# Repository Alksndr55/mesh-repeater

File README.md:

<div align="center">

# Mesh Repeater

### Плата LoRa-репитера для MeshCore и Meshtastic

**v1.26 · одна плата · 90 × 100 мм**

Солнечное питание · Na-ion 1S / LTO 2S · аппаратный watchdog

[Скачать готовый комплект](https://github.com/Alksndr55/mesh-repeater/releases/download/v1.26/Mesh_Repeater_v1.26_KiCad.zip) · [Релиз v1.26](https://github.com/Alksndr55/mesh-repeater/releases/tag/v1.26) · [Двухплатная версия v2](https://github.com/Alksndr55/mesh-repeater-2.0)

*3D-рендер проекта KiCad v1.26. Состав устанавливаемых компонентов зависит от выбранного варианта сборки.*

</div>

Mesh Repeater объединяет радиочасть, солнечный зарядник, питание и служебные узлы на одной плате. Устройство предназначено для самостоятельной сборки и питания от аккумулятора и солнечной панели.

**Главные цели проекта — максимальное энергосбережение и работа в суровых сибирских зимах.**

Ведущее исполнение **v1** удобно для монтажа и обслуживания: все узлы доступны на одной плате, без межплатного соединителя. Исходники KiCad, перечень компонентов и материалы для сборки входят в готовый комплект.

## Что предусмотрено

| Узел | Назначение |
|---|---|
| **nRF52840 + LoRa** | Доработанный NiceNano, модуль HT-RA62 на SX1262, антенный разъём SMA и место под фильтр FL1. |
| **Солнечный зарядник** | CN3722 с настройкой рабочей точки солнечной панели. |
| **Na-ion 1S или LTO 2S** | Три варианта комплектации: Na-ion 1S с COLD, Na-ion 1S без COLD, LTO 2S с пассивной балансировкой. |
| **Питание 3,3 В** | Повышающе-понижающий TPS63802, двухступенчатый LC-фильтр и отдельная ветвь питания радиомодуля. |
| **Контроль аккумулятора** | INA219 измеряет напряжение и ток в основном тракте аккумулятора. |
| **Часы и watchdog** | DS3231M с резервом от CR2032; ATtiny13A следит за активностью TXEN и может сбросить основной процессор. |
| **Подключение и обслуживание** | Разъём внешнего GPS, I²C и UART с логикой 3,3 В, AVR ISP, кнопки USER/RESET и контрольные точки. |

### Опциональный фильтр антенны

На MAIN предусмотрено место **FL1** для полосового SAW-фильтра **S869M000S003**. Он ослабляет внеполосные сигналы. В полосе 868–870 МГц паспортные потери составляют до 2,5 дБ. Штатный тракт проходит через медную перемычку **NT1**. Перед монтажом FL1 перемычку разрезают по инструкции и ограничивают мощность на входе фильтра до **+13 дБм**.

Рабочая температура этого фильтра **−10…+65 °C**. Для более холодных установок сохраняют штатный обход NT1. [Паспорт фильтра](https://abracon.com/datasheets/AEL-Crystals/PN/S869M000S003.pdf) · [Монтаж FL1](docs/ASSEMBLY_COMMON_RU.md)

## Совместимость с MeshCore и Meshtastic

Радиомодуль HT-RA62 (SX1262 с TCXO) подключён по распиновке **FakeTec / ProMicro nRF52840**. Для обеих версий платы подходят следующие профили прошивок.

| Прошивка | Профиль | Конфигурация |
|---|---|---|
| **MeshCore** | ProMicro nRF52840, сборка `ProMicro_repeater` | [MeshCore ProMicro](https://github.com/meshcore-dev/MeshCore/blob/repeater-v1.18.0/variants/promicro/platformio.ini#L40-L53) |
| **Meshtastic** | NRF52 Pro-micro DIY с TCXO, сборка `nrf52_promicro_diy_tcxo` | [Meshtastic ProMicro TCXO](https://github.com/meshtastic/firmware/blob/v2.7.26.54e0d8d/variants/nrf52840/diy/nrf52_promicro_diy_tcxo/platformio.ini) |

Совместимость проверена по распиновке и конфигурациям сборок. Показания напряжения аккумулятора калибруют под делитель платы **1:2**. Для Na-ion 1S и LTO 2S шкалу процента заряда адаптируют под химию и число ячеек. При подключении внешнего UART к J5 сверяют назначение RX и TX с выбранной прошивкой.

## Варианты сборки

| Вариант | Комплектация |
|---|---|
| **Na-ion 1S · COLD** | Узел температурного ограничения зарядного тока установлен. |
| **Na-ion 1S · без COLD** | Сборка без узла COLD. |
| **LTO · 2S** | Две последовательные ячейки LTO и пассивные балансиры. |

Вариант задаётся номиналами и составом деталей по BOM. Это выбор при сборке, а не переключение химии аккумулятора одной перемычкой. Условия заряда выбирают по паспорту конкретных ячеек; схема LTO не заменяет полноценную BMS.

### COLD — ограничение тока заряда на холоде

В сборке Na-ion 1S с COLD датчик TH1 задаёт температурный режим солнечного зарядника CN3722. При охлаждении схема включает дополнительный шунт R56 в цепь измерения тока. Расчётный предел зарядного тока снижается примерно с **0,67 А до 0,10 А**. При потеплении возвращается обычный режим.

Расчётный порог снижения тока — **−17,4 °C**, возврата — **−14,5 °C**. Разница между порогами помогает избежать частых переключений при колебаниях температуры. Один датчик TH1 устанавливают на плате или выносят к аккумулятору. Допустимый ток и температуру заряда сверяют с паспортом конкретной ячейки. [Общая инструкция по сборке](docs/ASSEMBLY_COMMON_RU.md)

### Watchdog — автоматический перезапуск репитера

Отдельный ATtiny13A с прошивкой watchdog v1.00 следит за сигналом **TXEN**, который показывает включение передатчика LoRa. Каждое новое включение передатчика запускает отсчёт заново. Между событиями контроллер спит в режиме Power-down. Когда время ожидания истекает, ATtiny13A подаёт импульс RESET на nRF52840. После сброса выбранная прошивка загружается заново и инициализирует радиомодуль.

При 3,3 В и комнатной температуре расчётные ориентиры составляют около **3,5 часа** ожидания и **1,2 секунды** сброса. При длительном молчании радиомодуля или застрявшем высоком TXEN тайм-аут тоже срабатывает. [Подключение и прошивка watchdog](v1/design/watchdog_reference/INTEGRATION_RU.txt)

## От схемы — к детали на плате

В ZIP уже включён **portable NexusBV**. Запуск `START.cmd` открывает меню с CAD и PDF-схемой нужной сборки. Двойной щелчок по обозначению или свободной части тела символа в PDF помогает найти компонент на бордвью.

- Два CAD: **NaIon_COLD** и **LTO_2S**, с номиналами и отметками DNP.
- PDF-схемы, BOM и инструкции по сборке.
- Проект KiCad 10 с локальными посадочными местами и всеми используемыми 3D-моделями.
- Watchdog v1.00: исходники, HEX и инструкция прошивки.

<details>
<summary><strong>Посмотреть обратную сторону платы</strong></summary>

</details>

## С чего начать

1. Скачайте **Mesh_Repeater_v1.26_KiCad.zip** из [релиза](https://github.com/Alksndr55/mesh-repeater/releases/tag/v1.26) и полностью распакуйте его.
2. Для просмотра запустите `START.cmd` в Windows; для редактирования откройте [проект MAIN](v1/design/Meshcore_NaIon/Meshcore_NaIon.kicad_pro) в KiCad 10.
3. Выберите вариант аккумулятора и собирайте плату по [BOM](v1/bom/COMPONENT_BOM.csv) и [общей инструкции](docs/ASSEMBLY_COMMON_RU.md).

**Перед первым включением:** модуль NiceNano требует указанной в инструкции доработки питания. Перед подключением USB нужно снять шунт **J11**, а вернуть его после отключения USB. J8 и J12 соединены с общей BAT: независимые аккумуляторы к ним одновременно не подключают.

## Документация

[Общая схема PDF](shared/output/pdf/MeshRepeater_schematic.pdf) · [Схема KiCad](shared/schematic/MeshRepeater.kicad_pro) · [Сборка v1](v1/docs/ASSEMBLY_RU.md) · [Аппаратные ограничения](docs/LIMITATIONS_RU.md) · [Изменения выпуска](https://github.com/Alksndr55/mesh-repeater/releases/tag/v1.26)

<details>
<summary><strong>Статус проекта и проверки</strong></summary>

Это предварительный инженерный выпуск. Для точных файлов v1.26 проверены общая схема, BOM, ERC/DRC, соответствие платы схеме и комплектность архива. Эти проверки не заменяют испытания собранного устройства: дальность связи, автономность, температурные режимы и работа конкретных модулей здесь не заявляются как измеренные характеристики.

[Отчёт проверок](v1/audit/current/checks.json) · [Экспорт CAD/PDF](v1/audit/current/exports.json) · [Манифест файлов](RELEASE_MANIFEST.json)

</details>

---

**Designed by @Alksndritm** · [Alksndr55](https://github.com/Alksndr55)

Собственные материалы — [CC BY-NC-SA 4.0](v1/LICENSE.md). Сторонние компоненты, модели и программы сохраняют свои лицензии.

Проекты прошивок — [MeshCore](https://github.com/meshcore-dev/MeshCore) и [Meshtastic](https://github.com/meshtastic/firmware).

## Поддержать проект

**Осциллограф Siglent SDS1204X HD.** Пульсации любят прятаться между цифрами мультиметра. Осциллограф поможет их поймать и проверить питание при запуске и передаче.

[Скинуться на осциллограф через Т‑Банк](https://t.tb.ru/pm_short/89zrJmEhG7B)

**Микроскоп Leica IVESTA 3.** У припоя иногда свой план монтажа. Под микроскопом удобнее паять мелкие детали и вовремя замечать перемычки между выводами.

[Скинуться на микроскоп через Сбер](https://messenger.sbrf.ru/sl/KsiFZJu4xBxTLGTPz)

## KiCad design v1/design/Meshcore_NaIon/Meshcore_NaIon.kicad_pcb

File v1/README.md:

# Mesh Repeater v1.26

Designed by @Alksndritm. Текущее исполнение общего проекта.
Ведущая разводка.
Предыдущий опубликованный выпуск от 30.10.2026: [v1.25 на GitHub](https://github.com/Alksndr55/mesh-repeater/releases/tag/v1.25).
Предыдущая публикация — [v1.22](https://github.com/Alksndr55/mesh-repeater/releases/tag/v1.22)
(прежнее обозначение S4.22). Локальная редакция от 06.11.2026 — v1.26. Следующий номер — v1.27.

[MAIN](design/Meshcore_NaIon/Meshcore_NaIon.kicad_pro)

[Общая схема](../shared/schematic/MeshRepeater.kicad_pro) ·
[BOM](bom/COMPONENT_BOM.csv) · [Сборка](docs/ASSEMBLY_RU.md) ·
[Порядок выпуска](../docs/WORKFLOW_RU.md) · [Лицензия](LICENSE.md).

Текущие экспорты находятся в output/current, проверки — в audit/current.
Версия и состав задаются корневым project.json. CAD остаётся редактируемым;
общий процесс выпуска сохраняет геометрию и проверяет соответствие общей схеме.
Опубликованные исторические теги сохраняют свои прежние имена.

Дорожки и GND-переходы приведены к [общим правилам](../docs/ROUTING_RULES_RU.md).
[Результат и исключения сетки](../docs/ROUTING_RESULT_RU.md).
Включён [watchdog v1.00](design/watchdog_reference/INTEGRATION_RU.txt)
с каноническими исходником и HEX; LFUSE=0x73, HFUSE=0xFB, ISP 100 мкс.
Локальный архив этого выпуска создаётся в `../releases/v1.26/`.

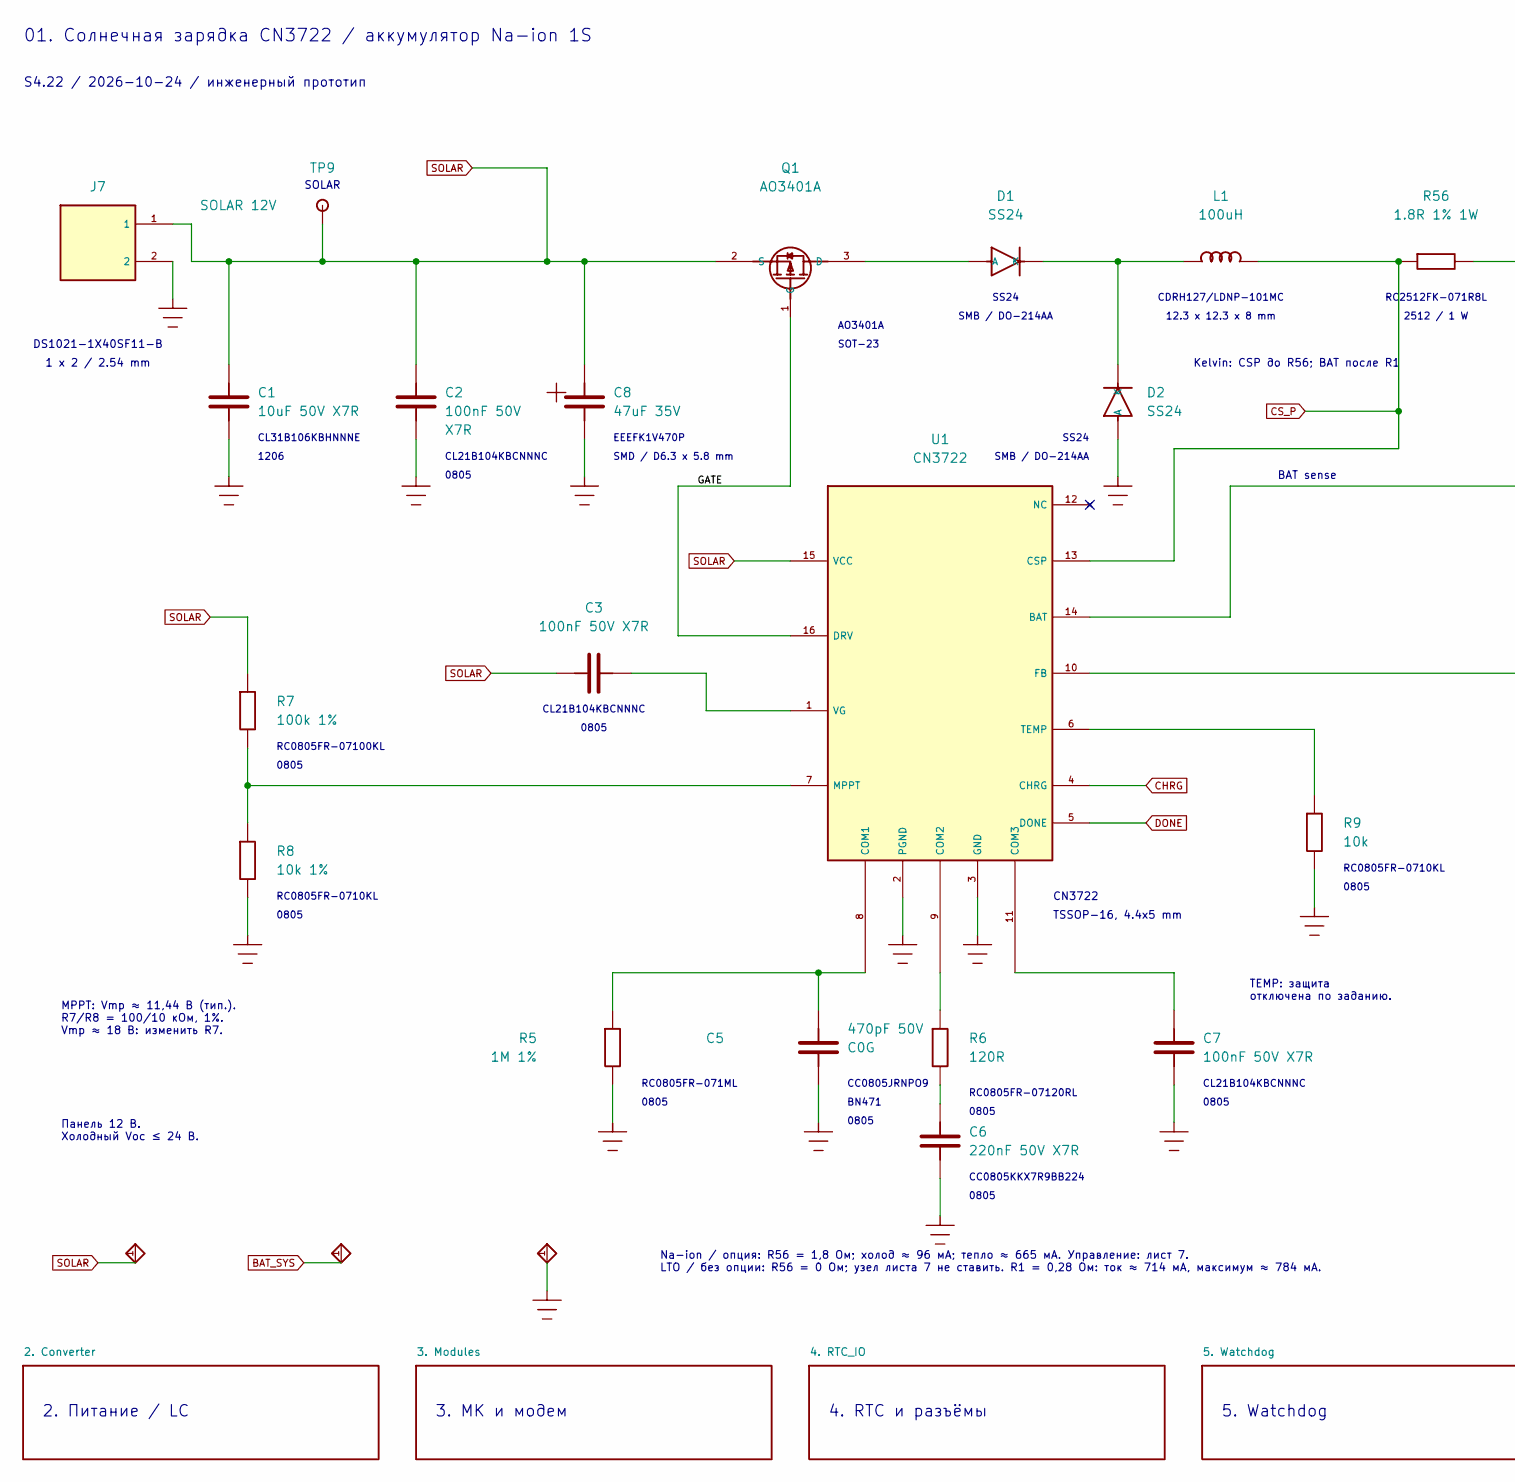
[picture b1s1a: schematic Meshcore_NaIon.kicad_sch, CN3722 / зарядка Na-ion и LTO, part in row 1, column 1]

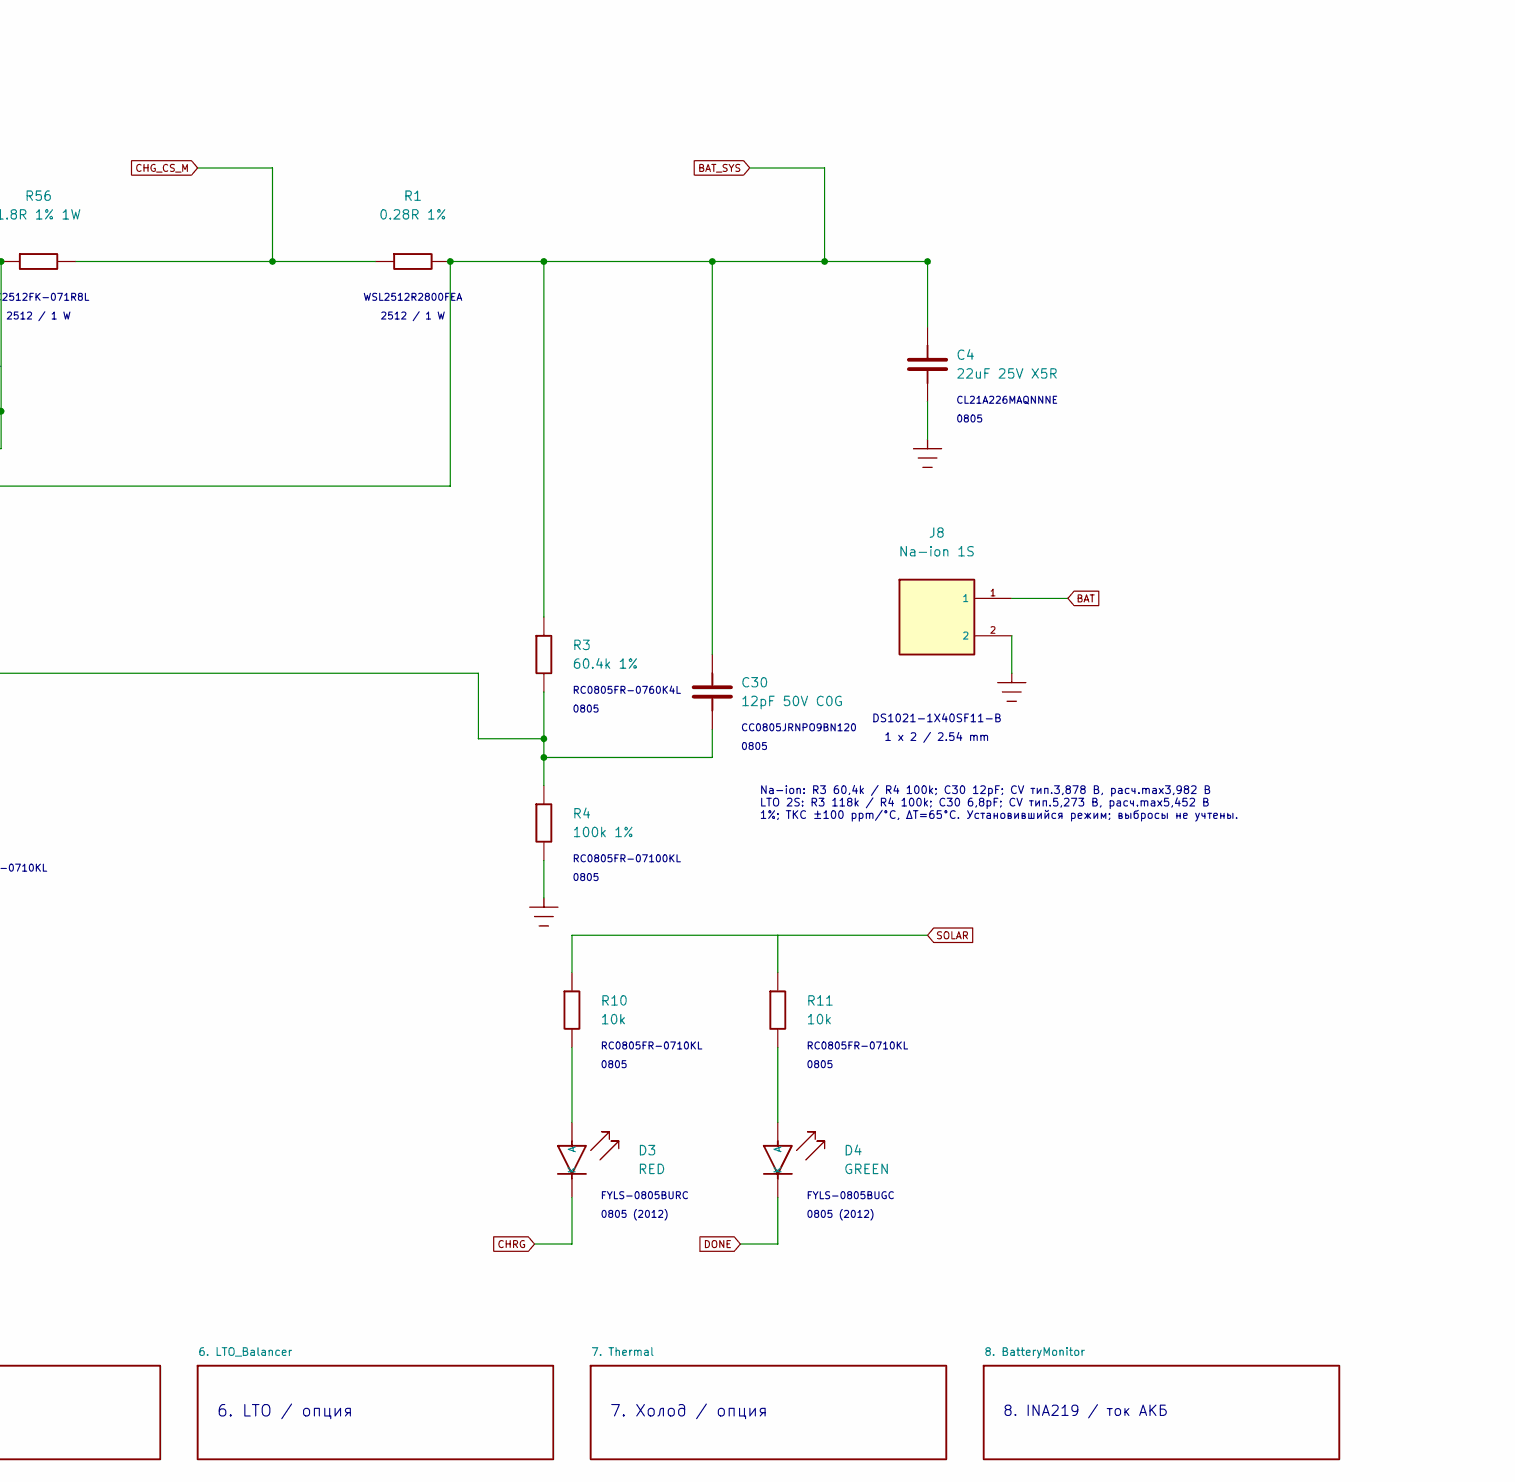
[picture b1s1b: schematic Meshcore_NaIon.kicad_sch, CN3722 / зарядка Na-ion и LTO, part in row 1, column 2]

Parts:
C1: 10uF 50V X7R; C_1206_3216Metric; MPN CL31B106KBHNNNE
C2, C3, C7: 100nF 50V X7R; C_0805_2012Metric; MPN CL21B104KBCNNNC
C4: 22uF 25V X5R; C_0805_2012Metric; MPN CL21A226MAQNNNE
C5: 470pF 50V C0G; C_0805_2012Metric; MPN CC0805JRNPO9BN471
C6: 220nF 50V X7R; C_0805_2012Metric; MPN CC0805KKX7R9BB224
C8: 47uF 35V; CP_Elec_Panasonic_FK_D_6.3x5.8; MPN EEEFK1V470P
C30: 12pF 50V C0G; C_0805_2012Metric; MPN CC0805JRNPO9BN120
D1, D2: SS24; D_SMB; MPN SS24
D3: RED; LED_0805_2012Metric; MPN FYLS-0805BURC
D4: GREEN; LED_0805_2012Metric; MPN FYLS-0805BUGC
J7: SOLAR 12V; PinHeader_1x02_P2.54mm_Vertical; MPN DS1021-1X40SF11-B
J8: Na-ion 1S; PinHeader_1x02_P2.54mm_Vertical; MPN DS1021-1X40SF11-B
L1: 100uH; L_Sumida_CDRH127_LDNP_101MC; MPN CDRH127/LDNP-101MC
Q1: AO3401A; SOT-23; MPN AO3401A
R1: 0.28R 1%; R_Vishay_WSL2512_A3__A3_R1; MPN WSL2512R2800FEA
R3: 60.4k 1%; R_0805_2012Metric; MPN RC0805FR-0760K4L; LCSC C2084414
R4: 100k 1%; R_0805_2012Metric; MPN RC0805FR-07100KL; LCSC C110775
R5: 1M 1%; R_0805_2012Metric; MPN RC0805FR-071ML
R6: 120R; R_0805_2012Metric; MPN RC0805FR-07120RL
R7: 100k 1%; R_0805_2012Metric; MPN RC0805FR-07100KL; LCSC C856623
R8: 10k 1%; R_0805_2012Metric; MPN RC0805FR-0710KL
R9, R10, R11: 10k; R_0805_2012Metric; MPN RC0805FR-0710KL
R56: 1.8R 1% 1W; R_2512_6332Metric__A3_R56; MPN RC2512FK-071R8L
TP9: SOLAR; TestPoint_Pad_D1.5mm; MPN PCB test pad / not purchased
U1: CN3722; TSSOP-16_4.4x5mm_P0.65mm; MPN CN3722; LCSC C77905

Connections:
/GATE: Q1.1 (G), U1.16 (DRV)
BAT: J8.1; also elsewhere on the board
BAT_SYS: C4.1, C30.1, R1.2, R3.1, U1.14 (BAT); also elsewhere on the board
CHG_CS_M: R1.1, R56.2; also elsewhere on the board
CHRG: D3.1 (K), U1.4 (CHRG)
CS_P: L1.2, R56.1, U1.13 (CSP); also elsewhere on the board
DONE: D4.1 (K), U1.5 (DONE)
GND: C1.2, C2.2, C4.2, C5.2, C6.2, C7.2, C8.2, D2.2 (A), J7.2, J8.2, R4.2, R5.2, R8.2, R9.2, U1.2 (PGND), U1.3 (GND); also elsewhere on the board
unnamed: C6.1, R6.2
unnamed: D1.2 (A), Q1.3 (D)
unnamed: D1.1 (K), D2.1 (K), L1.1
unnamed: D3.2 (A), R10.2
unnamed: D4.2 (A), R11.2
unnamed: C5.1, R5.1, U1.8 (COM1)
unnamed: R6.1, U1.9 (COM2)
unnamed: C7.1, U1.11 (COM3)
unnamed: C30.2, R3.2, R4.1, U1.10 (FB)
unnamed: R7.2, R8.1, U1.7 (MPPT)
unnamed: R9.1, U1.6 (TEMP)
unnamed: C3.2, U1.1 (VG)
SOLAR: C1.1, C2.1, C3.1, C8.1, J7.1, Q1.2 (S), R7.1, R10.1, R11.1, TP9.1, U1.15 (VCC); also elsewhere on the board

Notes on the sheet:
0805
RC0805FR-07120RL
Kelvin: CSP до R56; BAT после R1
EEEFK1V470P
WSL2512R2800FEA
3. МК и модем
2512 / 1 W
TEMP: защита отключена по заданию.
8. INA219 / ток АКБ
0805 (2012)
1206
SMB / DO-214AA
RC0805FR-07100KL
DS1021-1X40SF11-B
SOT-23
CL21A226MAQNNNE
6. LTO / опция
CL21B104KBCNNNC
1 x 2 / 2.54 mm
Na-ion: R3 60,4k / R4 100k; C30 12pF; CV тип.3,878 В, расч.max3,982 В LTO 2S: R3 118k / R4 100k; C30 6,8pF; CV тип.5,273 В, расч.max5,452 В 1%; ТКС ±100 ppm/°C, ΔT=65°C. Установившийся режим; выбросы не учтены.
4. RTC и разъёмы
FYLS-0805BURC
TSSOP-16, 4.4x5 mm
FYLS-0805BUGC
RC2512FK-071R8L
RC0805FR-0710KL
SS24
AO3401A
RC0805FR-0760K4L
CC0805KKX7R9BB224
CC0805JRNPO9BN120
S4.22 / 2026-10-24 / инженерный прототип
Панель 12 В. Холодный Voc ≤ 24 В.
CL31B106KBHNNNE
SMD / D6.3 x 5.8 mm
SOLAR
BAT sense
01. Солнечная зарядка CN3722 / аккумулятор Na-ion 1S
MPPT: Vmp ≈ 11,44 В (тип.). R7/R8 = 100/10 кОм, 1%. Vmp ≈ 18 В: изменить R7.
5. Watchdog

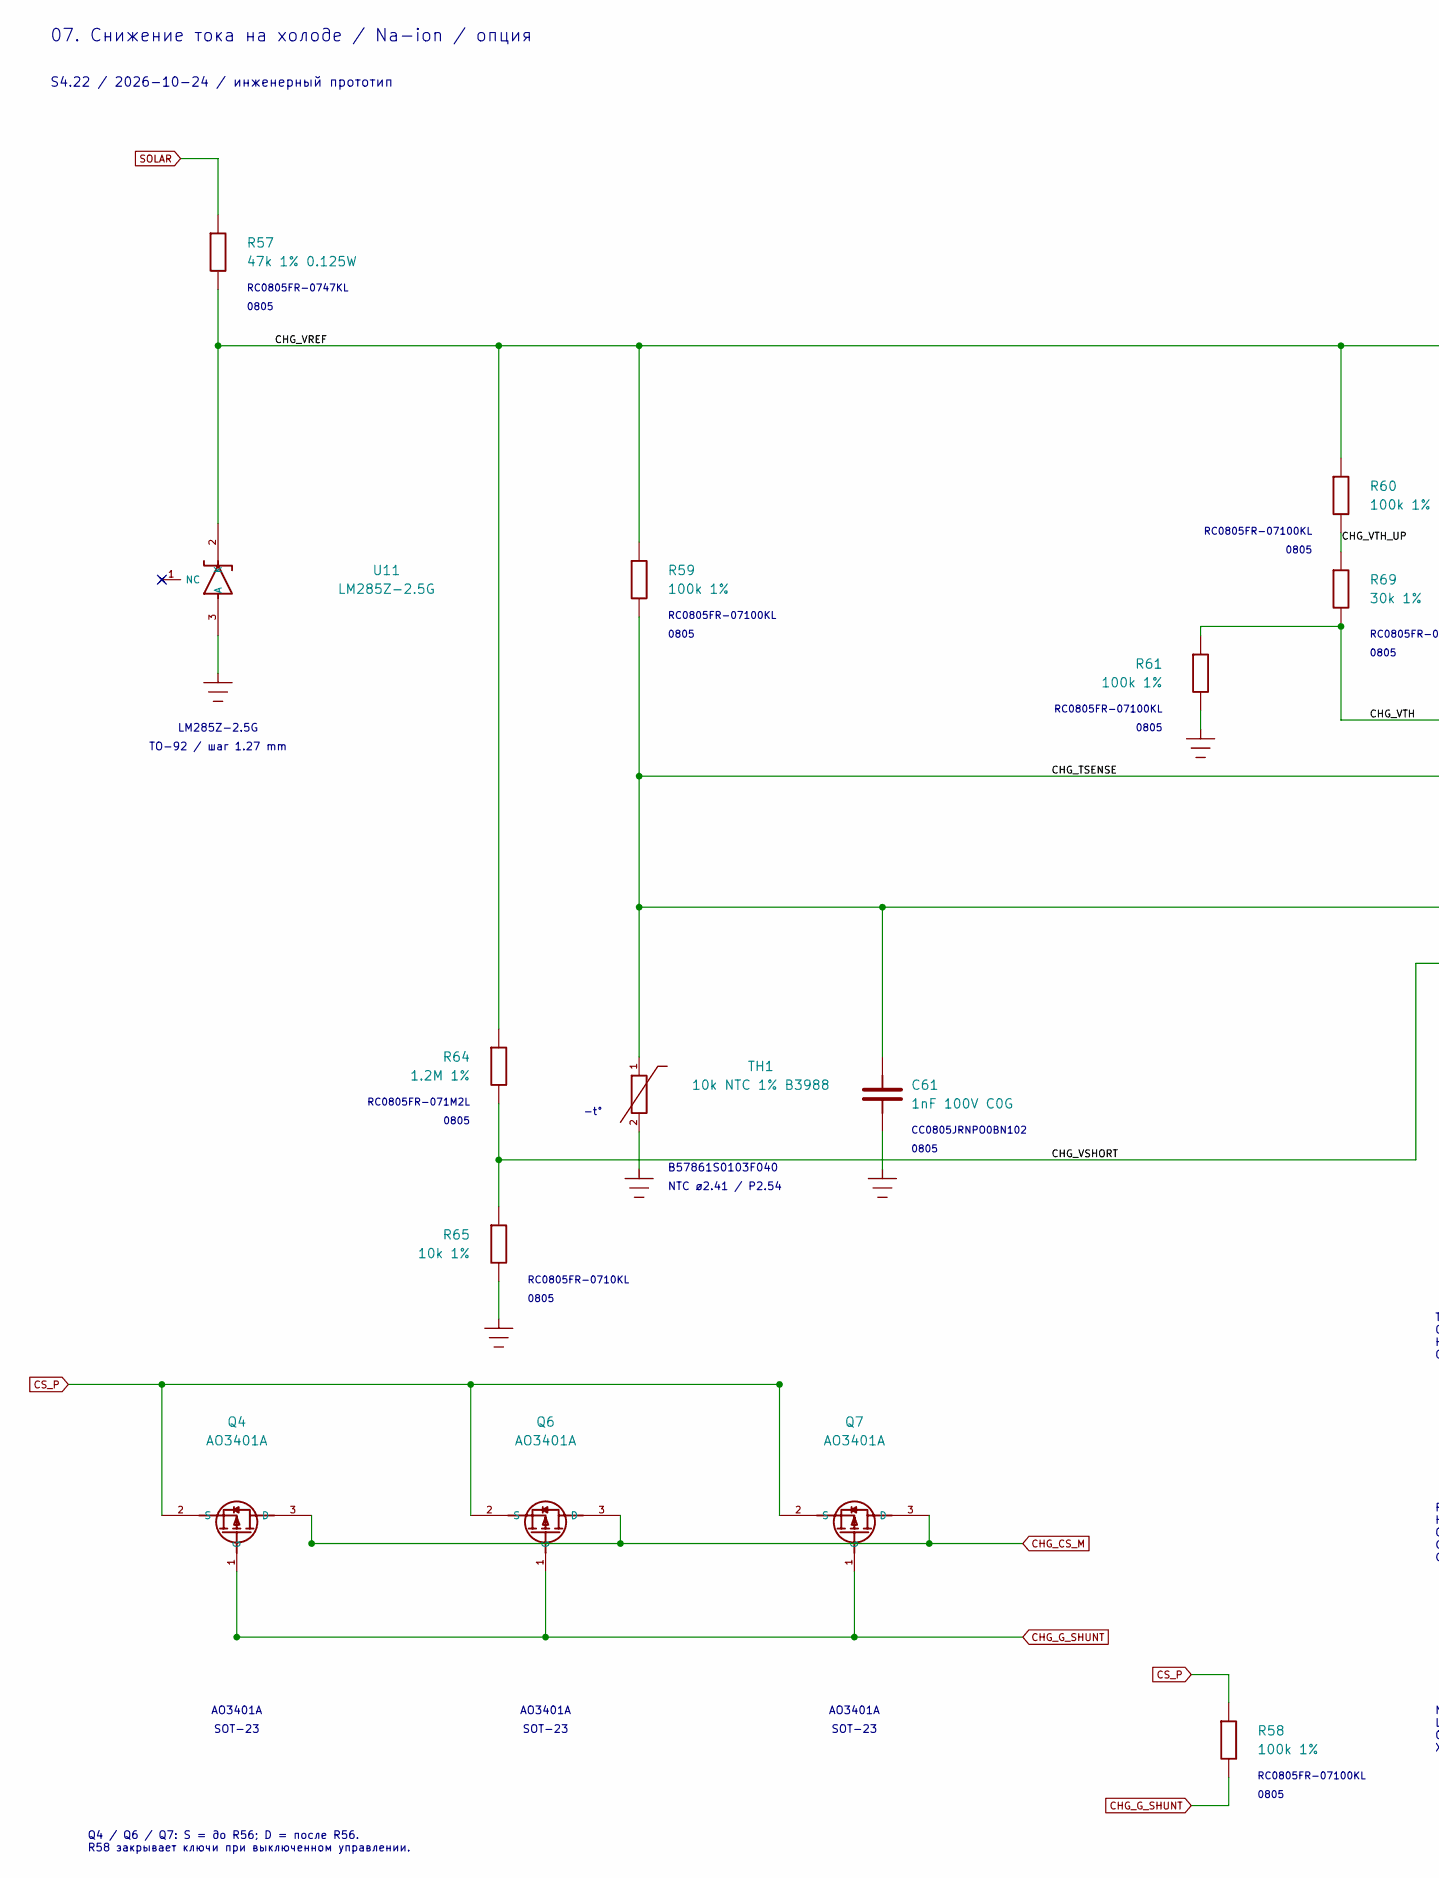
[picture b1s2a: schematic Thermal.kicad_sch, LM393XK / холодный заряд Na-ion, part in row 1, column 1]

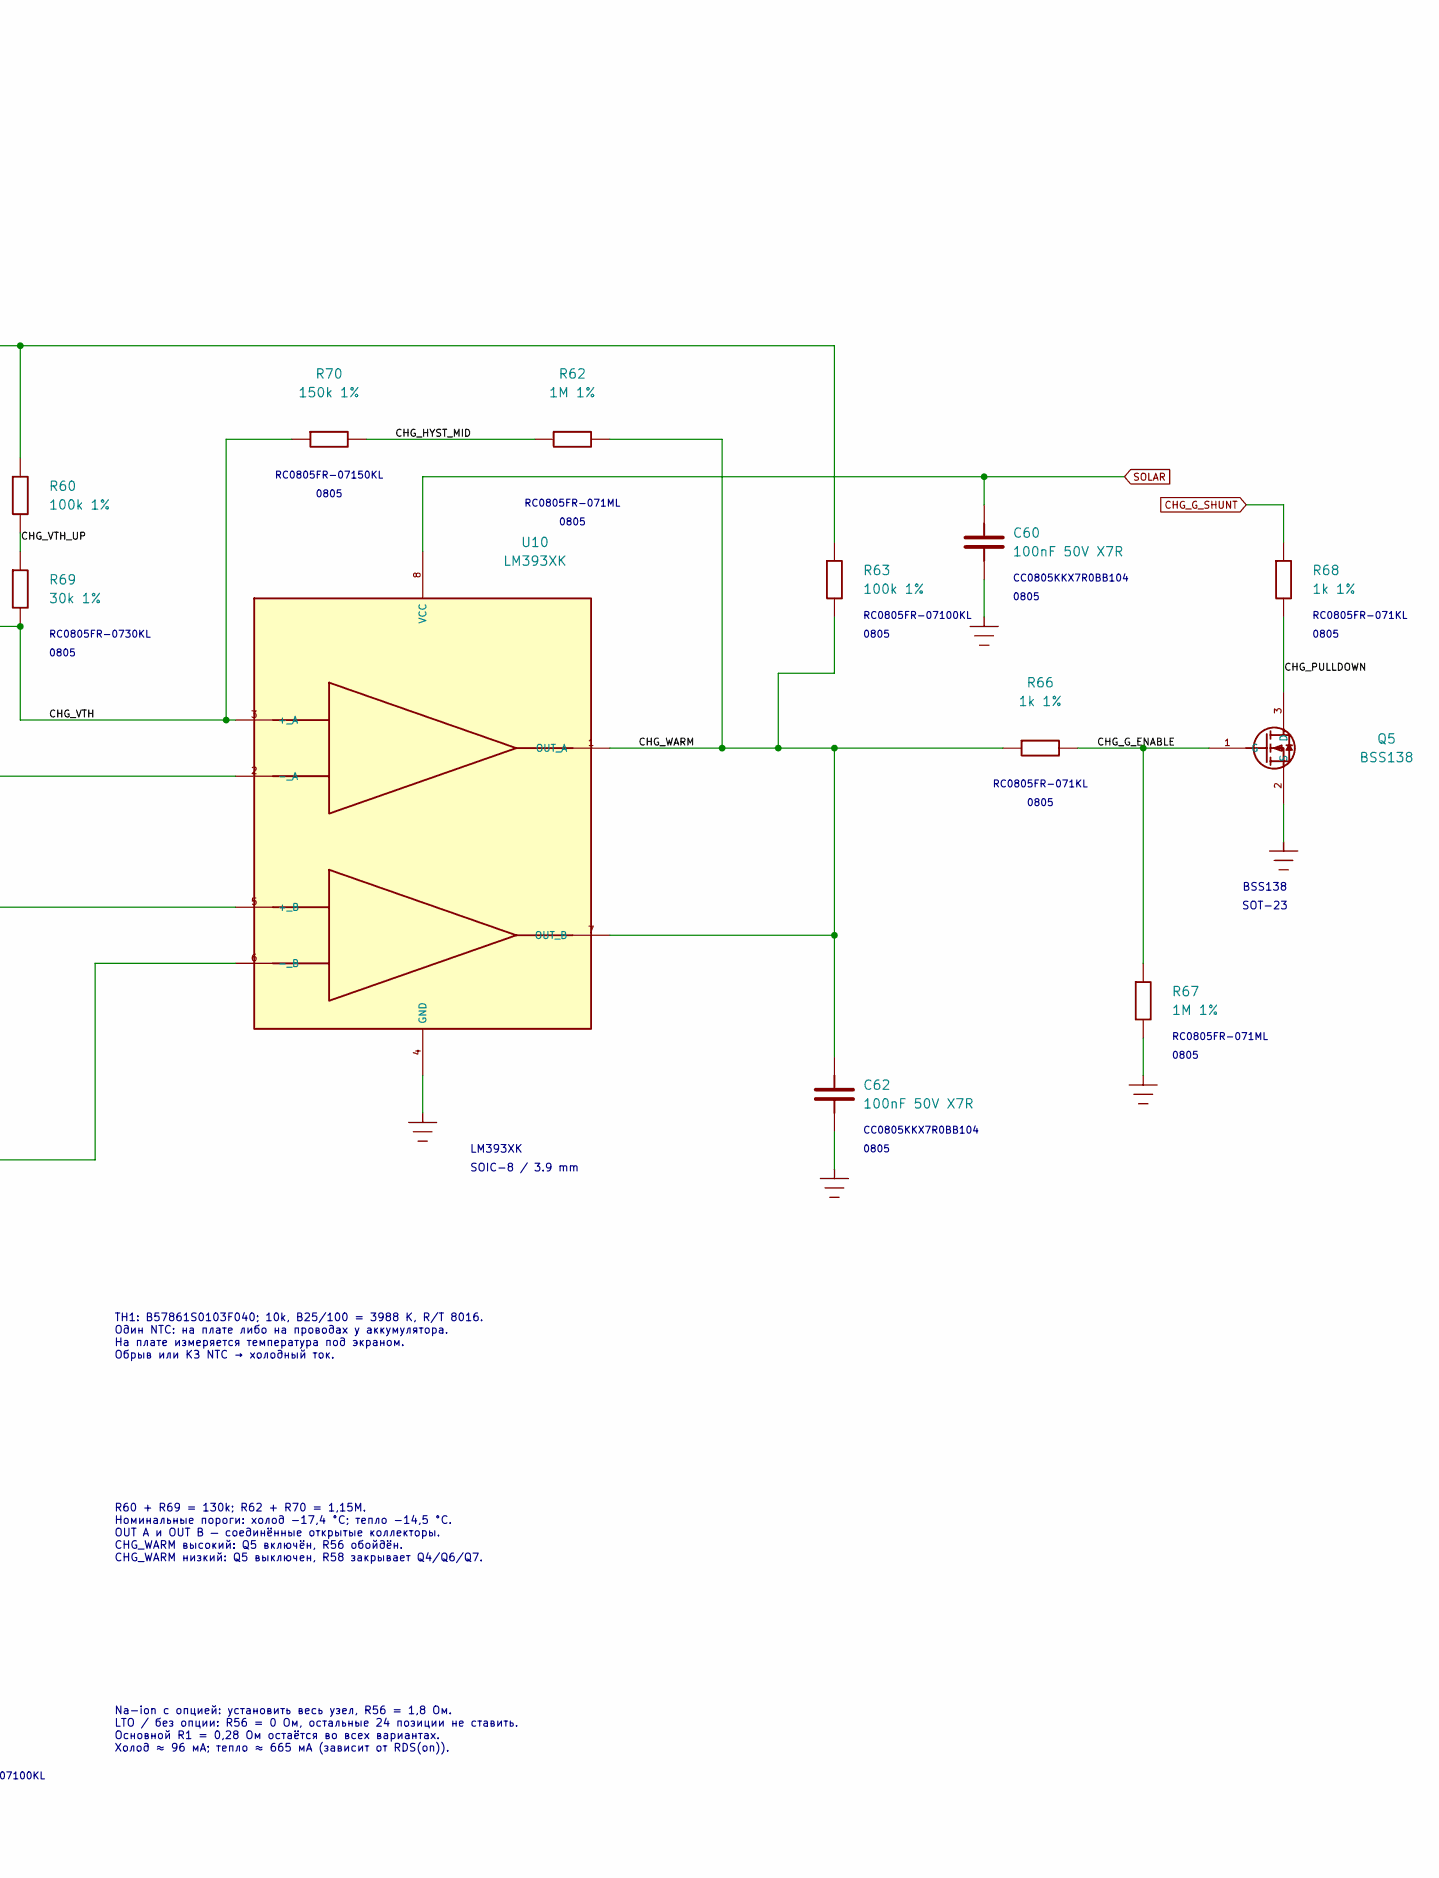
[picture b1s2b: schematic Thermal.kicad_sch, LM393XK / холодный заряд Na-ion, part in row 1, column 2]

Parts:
C60, C62: 100nF 50V X7R; C_0805_2012Metric; MPN CL21B104KBCNNNC
C61: 1nF 100V C0G; C_0805_2012Metric; MPN CC0805JRNPO0BN102
Q4, Q6, Q7: AO3401A; SOT-23; MPN AO3401A
Q5: BSS138; SOT-23; MPN BSS138
R57: 47k 1% 0.125W; R_0805_2012Metric; MPN RC0805FR-0747KL
R58, R59, R60, R61, R63: 100k 1%; R_0805_2012Metric; MPN RC0805FR-07100KL
R62, R67: 1M 1%; R_0805_2012Metric; MPN RC0805FR-071ML
R64: 1.2M 1%; R_0805_2012Metric; MPN RC0805FR-071M2L
R65: 10k 1%; R_0805_2012Metric; MPN RC0805FR-0710KL
R66, R68: 1k 1%; R_0805_2012Metric; MPN RC0805FR-071KL
R69: 30k 1%; R_0805_2012Metric; MPN RC0805FR-0730KL
R70: 150k 1%; R_0805_2012Metric; MPN RC0805FR-07150KL
TH1: 10k NTC 1% B3988; NTC_TDK_B57861S_Onboard_or_Remote_P2.54mm; MPN B57861S0103F040
U10: LM393XK; SOIC-8_3.9x4.9mm_P1.27mm; MPN LM393XK
U11: LM285Z-2.5G; TO-92_Inline; MPN LM285Z-2.5G

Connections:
/7. Thermal/CHG_G_ENABLE: Q5.1, R66.2, R67.1
/7. Thermal/CHG_HYST_MID: R62.2, R70.1
/7. Thermal/CHG_PULLDOWN: Q5.3, R68.2
/7. Thermal/CHG_TSENSE: C61.1, R59.2, TH1.1, U10.2, U10.5
/7. Thermal/CHG_VREF: R57.2, R59.1, R60.1, R63.1, R64.1, U11.2
/7. Thermal/CHG_VSHORT: R64.2, R65.1, U10.6
/7. Thermal/CHG_VTH: R61.1, R69.2, R70.2, U10.3
/7. Thermal/CHG_VTH_UP: R60.2, R69.1
/7. Thermal/CHG_WARM: C62.1, R62.1, R63.2, R66.1, U10.1, U10.7
CHG_CS_M: Q4.3, Q6.3, Q7.3; also elsewhere on the board
CHG_G_SHUNT: Q4.1, Q6.1, Q7.1, R58.2, R68.1
CS_P: Q4.2, Q6.2, Q7.2, R58.1; also elsewhere on the board
GND: C60.2, C61.2, C62.2, Q5.2, R61.2, R65.2, R67.2, TH1.2, U10.4, U11.3; also elsewhere on the board
SOLAR: C60.1, R57.1, U10.8; also elsewhere on the board

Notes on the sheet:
R60 + R69 = 130k; R62 + R70 = 1,15M. Номинальные пороги: холод −17,4 °C; тепло −14,5 °C. OUT A и OUT B — соединённые открытые коллекторы. CHG_WARM высокий: Q5 включён, R56 обойдён. CHG_WARM низкий: Q5 выключен, R58 закрывает Q4/Q6/Q7.
Q4 / Q6 / Q7: S = до R56; D = после R56. R58 закрывает ключи при выключенном управлении.
SOT-23
RC0805FR-0730KL
Na-ion с опцией: установить весь узел, R56 = 1,8 Ом. LTO / без опции: R56 = 0 Ом, остальные 24 позиции не ставить. Основной R1 = 0,28 Ом остаётся во всех вариантах. Холод ≈ 96 мА; тепло ≈ 665 мА (зависит от RDS(on)).
CC0805JRNPO0BN102
0805
NTC ø2.41 / P2.54
07. Снижение тока на холоде / Na-ion / опция
RC0805FR-07100KL
RC0805FR-071KL
RC0805FR-071ML
AO3401A
TH1: B57861S0103F040; 10k, B25/100 = 3988 K, R/T 8016. Один NTC: на плате либо на проводах у аккумулятора. На плате измеряется температура под экраном. Обрыв или КЗ NTC → холодный ток.
LM393XK
RC0805FR-0710KL
BSS138
-t°
RC0805FR-07150KL
S4.22 / 2026-10-24 / инженерный прототип
RC0805FR-071M2L
B57861S0103F040
RC0805FR-0747KL
SOIC-8 / 3.9 mm
TO-92 / шаг 1.27 mm
CC0805KKX7R0BB104
LM285Z-2.5G

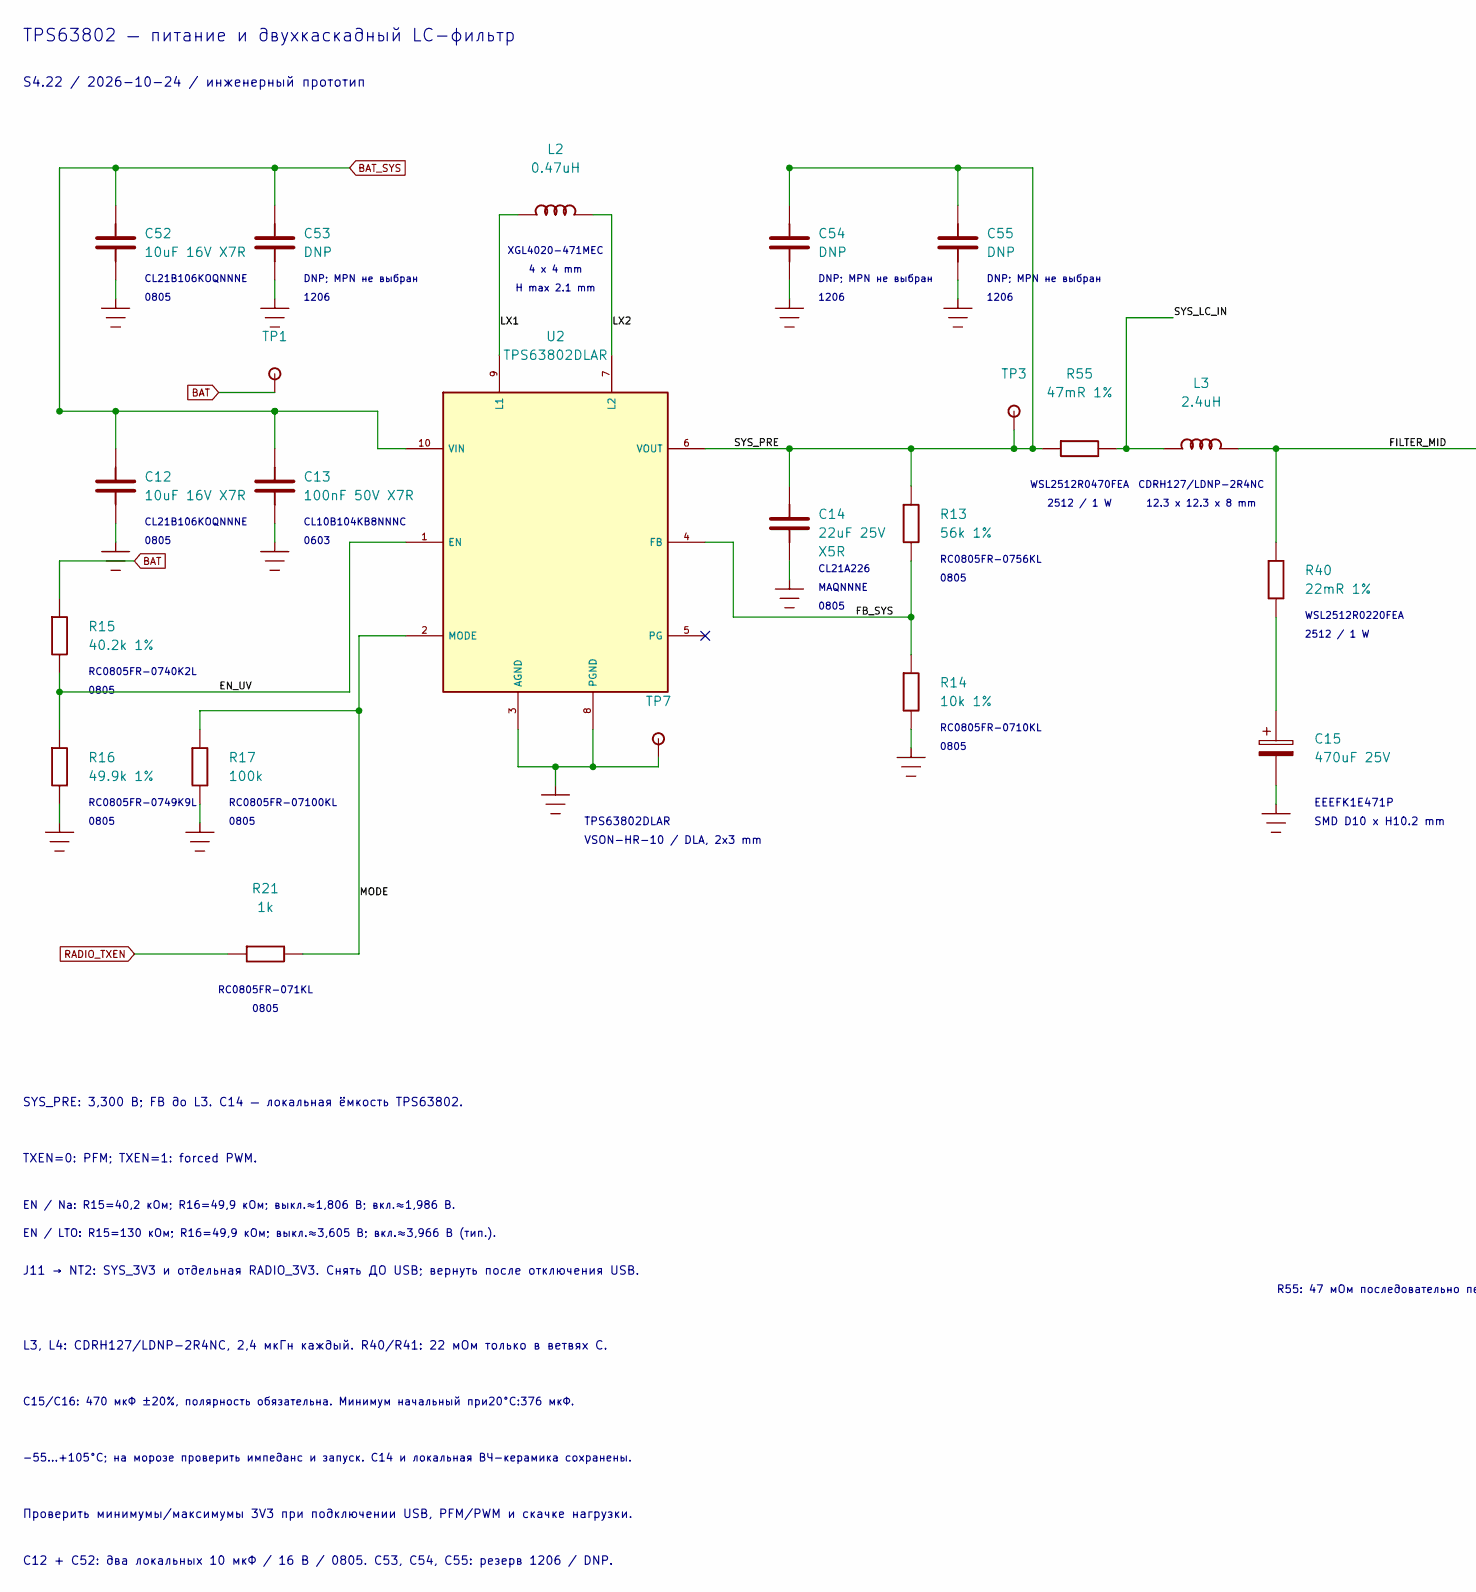
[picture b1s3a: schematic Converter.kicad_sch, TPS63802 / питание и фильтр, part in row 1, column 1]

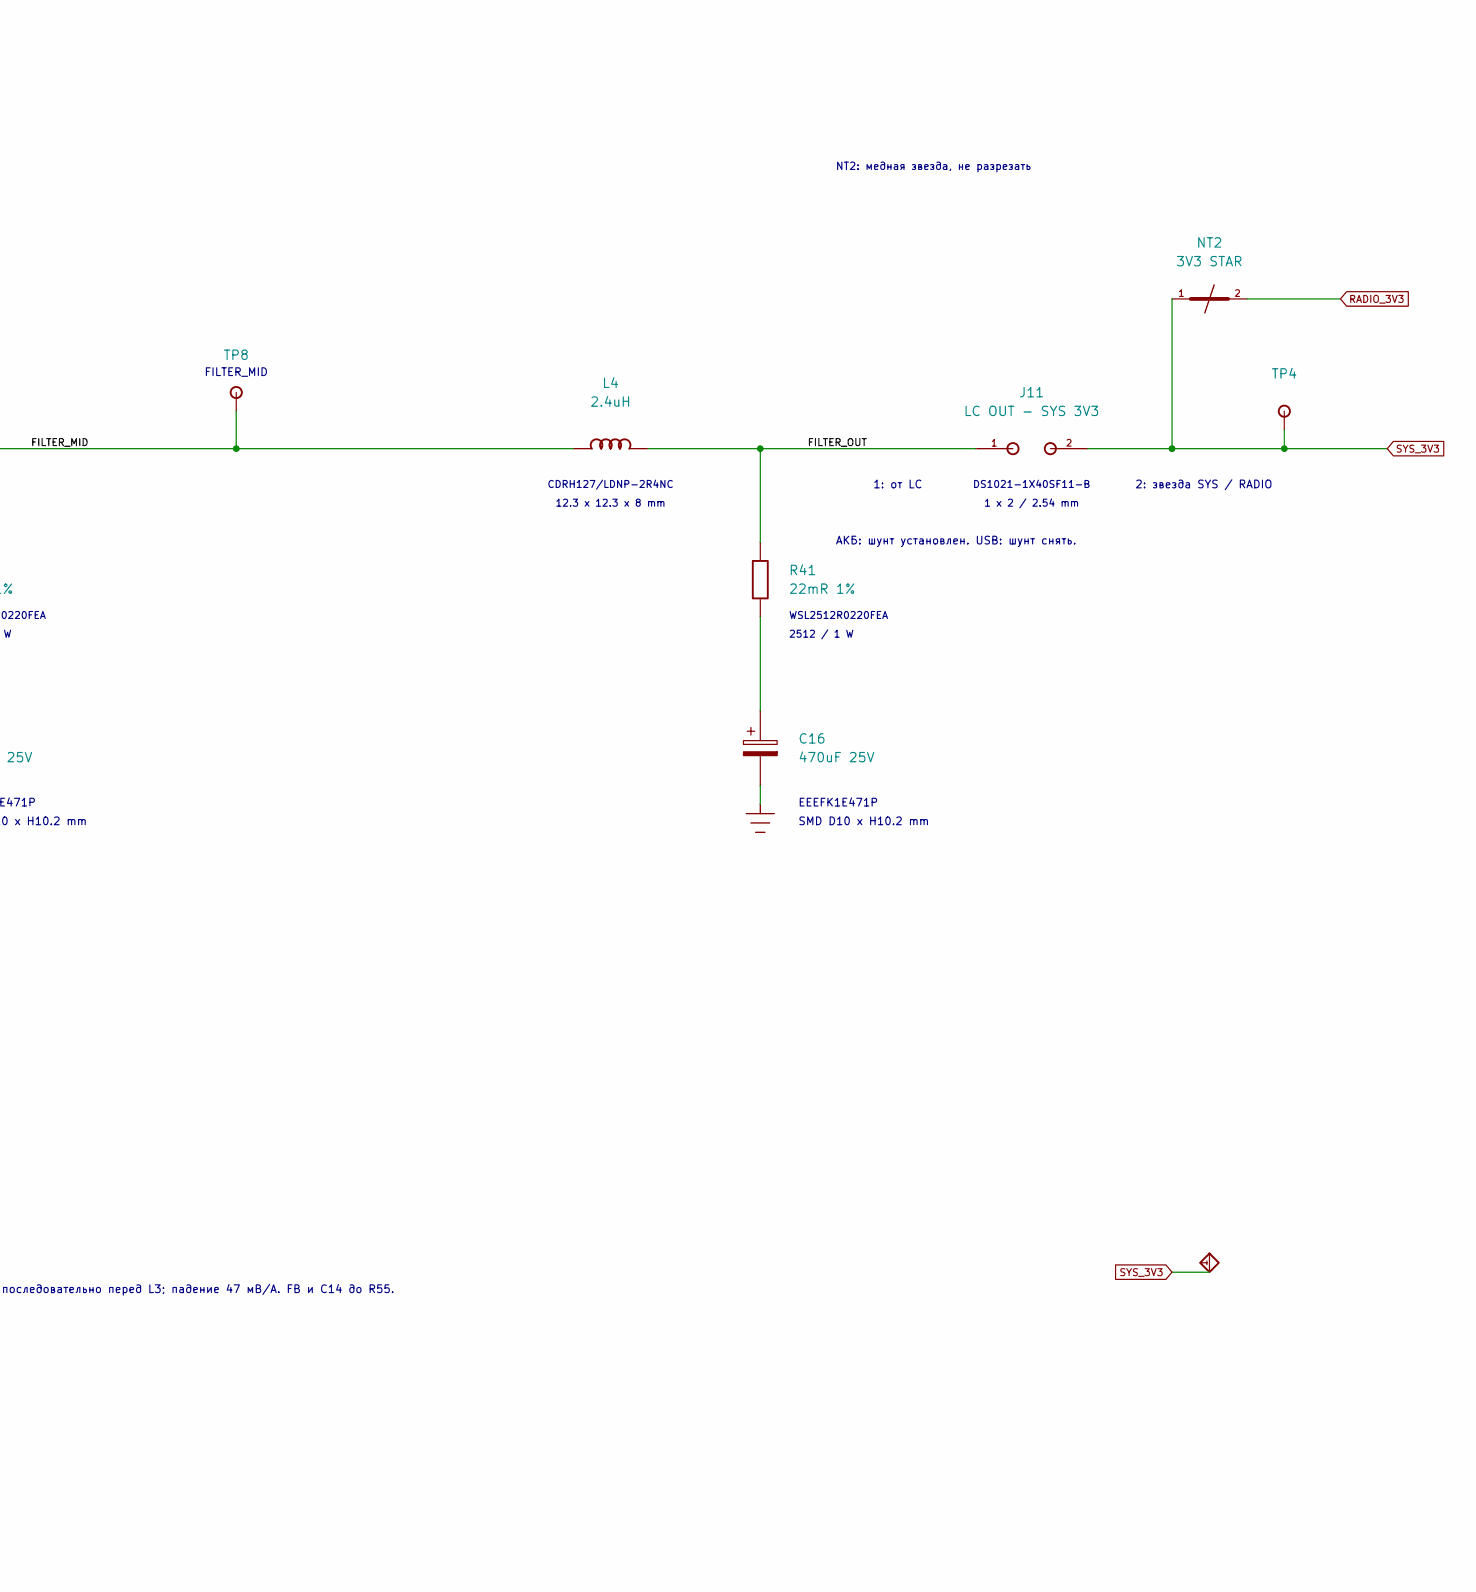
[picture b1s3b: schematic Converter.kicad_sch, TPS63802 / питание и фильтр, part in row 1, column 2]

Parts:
C12, C52: 10uF 16V X7R; C_0805_2012Metric; MPN CL21B106KOQNNNE
C13: 100nF 50V X7R; C_0805_2012Metric; MPN CL21B104KBCNNNC
C14: 22uF 25V X5R; C_0805_2012Metric; MPN CL21A226MAQNNNE
C15, C16: 470uF 25V; CP_Elec_10x10.2; MPN EEEFK1E471P
C53, C54, C55: DNP; C_1206_3216Metric
J11: LC OUT - SYS 3V3; PinHeader_1x02_P2.54mm_Vertical; MPN DS1021-1X40SF11-B
L2: 0.47uH; L_Coilcraft_XGL4020_471MEC_HandSolderUniversal; MPN XGL4020-471MEC; LCSC C5837785
L3, L4: 2.4uH; L_Sumida_CDRH127_LD; MPN CDRH127/LDNP-2R4NC
NT2: 3V3 STAR; NetTie_2_SMD_Power_Star_A3
R13: 56k 1%; R_0805_2012Metric; MPN RC0805FR-0756KL; LCSC C2523584
R14: 10k 1%; R_0805_2012Metric; MPN RC0805FR-0710KL
R15: 40.2k 1%; R_0805_2012Metric; MPN RC0805FR-0740K2L; LCSC C865475
R16: 49.9k 1%; R_0805_2012Metric; MPN RC0805FR-0749K9L; LCSC C469661
R17: 100k; R_0805_2012Metric; MPN RC0805FR-07100KL
R21: 1k; R_0805_2012Metric; MPN RC0805FR-071KL
R40: 22mR 1%; R_Vishay_WSL2512_A3__A3_R40; MPN WSL2512R0220FEA
R41: 22mR 1%; R_Vishay_WSL2512_A3__A3_R41; MPN WSL2512R0220FEA
R55: 47mR 1%; R_Vishay_WSL2512_A3__A3_R55; MPN WSL2512R0470FEA
TP1: BAT; TestPoint_Pad_D1.5mm
TP3: SYS_PRE; TestPoint_Pad_D1.5mm
TP4: SYS_3V3; TestPoint_Pad_D1.5mm
TP7: GND; TestPoint_Pad_D1.5mm
TP8: FILTER_MID; TestPoint_Pad_D1.5mm; MPN PCB test pad / not purchased
U2: TPS63802DLAR; TPS63802_DLA0010A; MPN TPS63802DLAR; LCSC C2845237

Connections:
/2. Converter/EN_UV: R15.2, R16.1, U2.1 (EN)
/2. Converter/FB_SYS: R13.2, R14.1, U2.4 (FB)
/2. Converter/FILTER_MID: L3.2, L4.1, R40.1, TP8.1
/2. Converter/FILTER_OUT: J11.1, L4.2, R41.1
/2. Converter/LX1: L2.1, U2.9 (L1)
/2. Converter/LX2: L2.2, U2.7 (L2)
/2. Converter/MODE: R17.1, R21.2, U2.2 (MODE)
/2. Converter/SYS_LC_IN: L3.1, R55.2
/2. Converter/SYS_PRE: C14.1, C54.1, C55.1, R13.1, R55.1, TP3.1, U2.6 (VOUT)
BAT: R15.1, TP1.1; also elsewhere on the board
BAT_SYS: C12.1, C13.1, C52.1, C53.1, U2.10 (VIN); also elsewhere on the board
GND: C12.2, C13.2, C14.2, C15.2, C16.2, C52.2, C53.2, C54.2, C55.2, R14.2, R16.2, R17.2, TP7.1, U2.3 (AGND), U2.8 (PGND); also elsewhere on the board
unnamed: C15.1, R40.2
unnamed: C16.1, R41.2
RADIO_3V3: NT2.2; also elsewhere on the board
RADIO_TXEN: R21.1; also elsewhere on the board
SYS_3V3: J11.2, NT2.1, TP4.1; also elsewhere on the board

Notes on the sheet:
EN / Na: R15=40,2 кОм; R16=49,9 кОм; выкл.≈1,806 В; вкл.≈1,986 В.
CDRH127/LDNP-2R4NC
0805
TXEN=0: PFM; TXEN=1: forced PWM.
TPS63802 — питание и двухкаскадный LC-фильтр
CL10B104KB8NNNC
WSL2512R0470FEA
1206
WSL2512R0220FEA
RC0805FR-07100KL
Проверить минимумы/максимумы 3V3 при подключении USB, PFM/PWM и скачке нагрузки.
DNP; MPN не выбран
MAQNNNE
АКБ: шунт установлен. USB: шунт снять.
CL21B106KOQNNNE
RC0805FR-071KL
TPS63802DLAR
1: от LC
4 x 4 mm
0603
C12 + C52: два локальных 10 мкФ / 16 В / 0805. C53, C54, C55: резерв 1206 / DNP.
1 x 2 / 2.54 mm
2: звезда SYS / RADIO
EN / LTO: R15=130 кОм; R16=49,9 кОм; выкл.≈3,605 В; вкл.≈3,966 В (тип.).
RC0805FR-0749K9L
12.3 x 12.3 x 8 mm
RC0805FR-0756KL
2512 / 1 W
J11 → NT2: SYS_3V3 и отдельная RADIO_3V3. Снять ДО USB; вернуть после отключения USB.
H max 2.1 mm
RC0805FR-0710KL
CL21A226
DS1021-1X40SF11-B
RC0805FR-0740K2L
NT2: медная звезда, не разрезать
SYS_PRE: 3,300 В; FB до L3. C14 — локальная ёмкость TPS63802.
XGL4020-471MEC
L3, L4: CDRH127/LDNP-2R4NC, 2,4 мкГн каждый. R40/R41: 22 мОм только в ветвях C.
FILTER_MID
VSON-HR-10 / DLA, 2x3 mm
